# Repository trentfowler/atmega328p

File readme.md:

# Skeleton for ATmega328p based microcontroller projects

**Description:** KiCad project files that can be used as the starting point for an ATmega328p based microcontroller pcb project

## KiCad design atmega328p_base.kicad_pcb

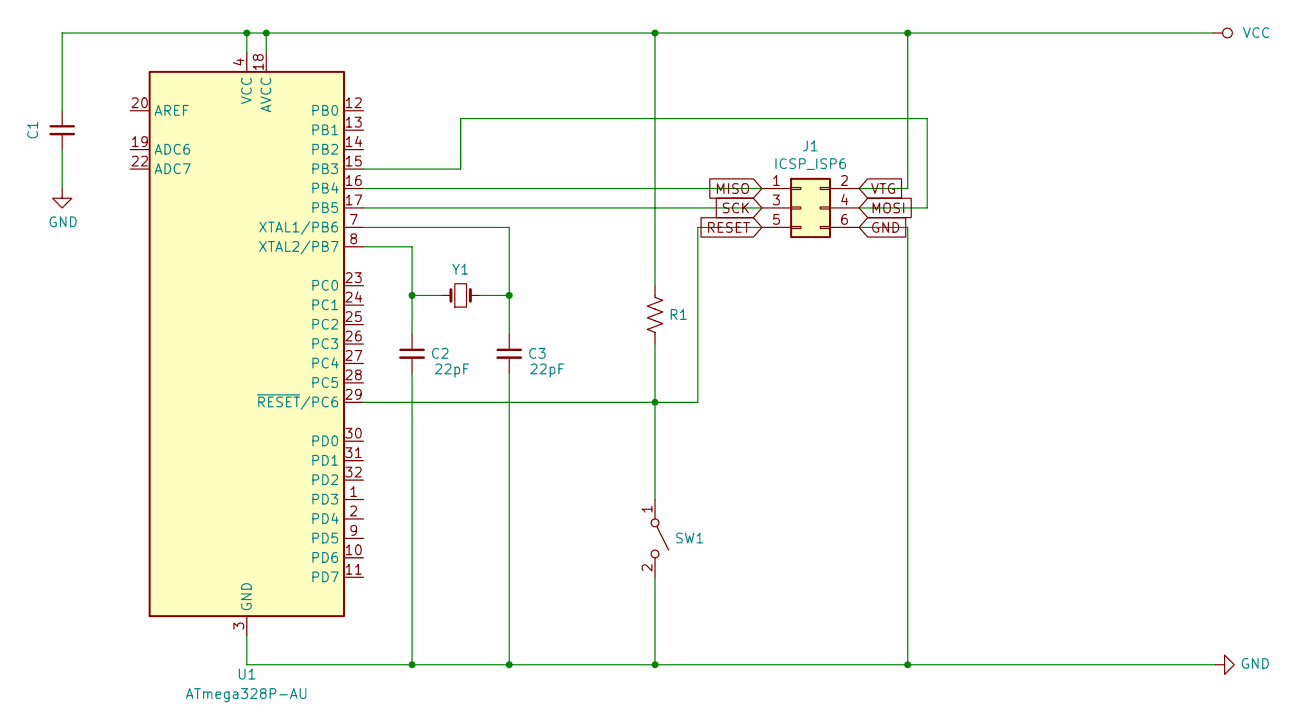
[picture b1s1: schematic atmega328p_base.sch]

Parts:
C1: 100nF; C_0805_2012Metric_Pad1.15x1.40mm_HandSolder
C2, C3: 22pF; C_0805_2012Metric_Pad1.15x1.40mm_HandSolder
J1: ICSP_ISP6; PinHeader_2x03_P2.00mm_Vertical
R1: 10K; R_0805_2012Metric_Pad1.15x1.40mm_HandSolder
SW1: SPST; SW_PUSH_6mm_H5mm
U1: ATmega328P-AU; TQFP-32_7x7mm_P0.8mm
Y1: 16MHz; Crystal_HC49-4H_Vertical

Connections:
GND: C1.2, C2.2, C3.2, J1.6, SW1.2 (B), U1.3 (GND), U1.5 (GND), U1.21 (GND); also elsewhere on the board
MISO: J1.1, U1.16 (PB4)
MOSI: J1.4, U1.15 (PB3)
unnamed: C2.1, U1.8 (XTAL2/PB7), Y1.1
unnamed: C3.1, U1.7 (XTAL1/PB6), Y1.2
RESET: J1.5, R1.2, SW1.1 (A), U1.29 (~RESET~/PC6)
SCK: J1.3, U1.17 (PB5)
VTG: C1.1, J1.2, R1.1, U1.4 (VCC), U1.6 (VCC), U1.18 (AVCC); also elsewhere on the board

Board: 2 copper layers, 9 parts (0 on the bottom side), 8 nets, no tracks yet.

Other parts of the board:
U2: LM7805; TO-220-3_Horizontal_TabDown

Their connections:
GND: U2.2; also elsewhere on the board
VTG: U2.3; also elsewhere on the board
